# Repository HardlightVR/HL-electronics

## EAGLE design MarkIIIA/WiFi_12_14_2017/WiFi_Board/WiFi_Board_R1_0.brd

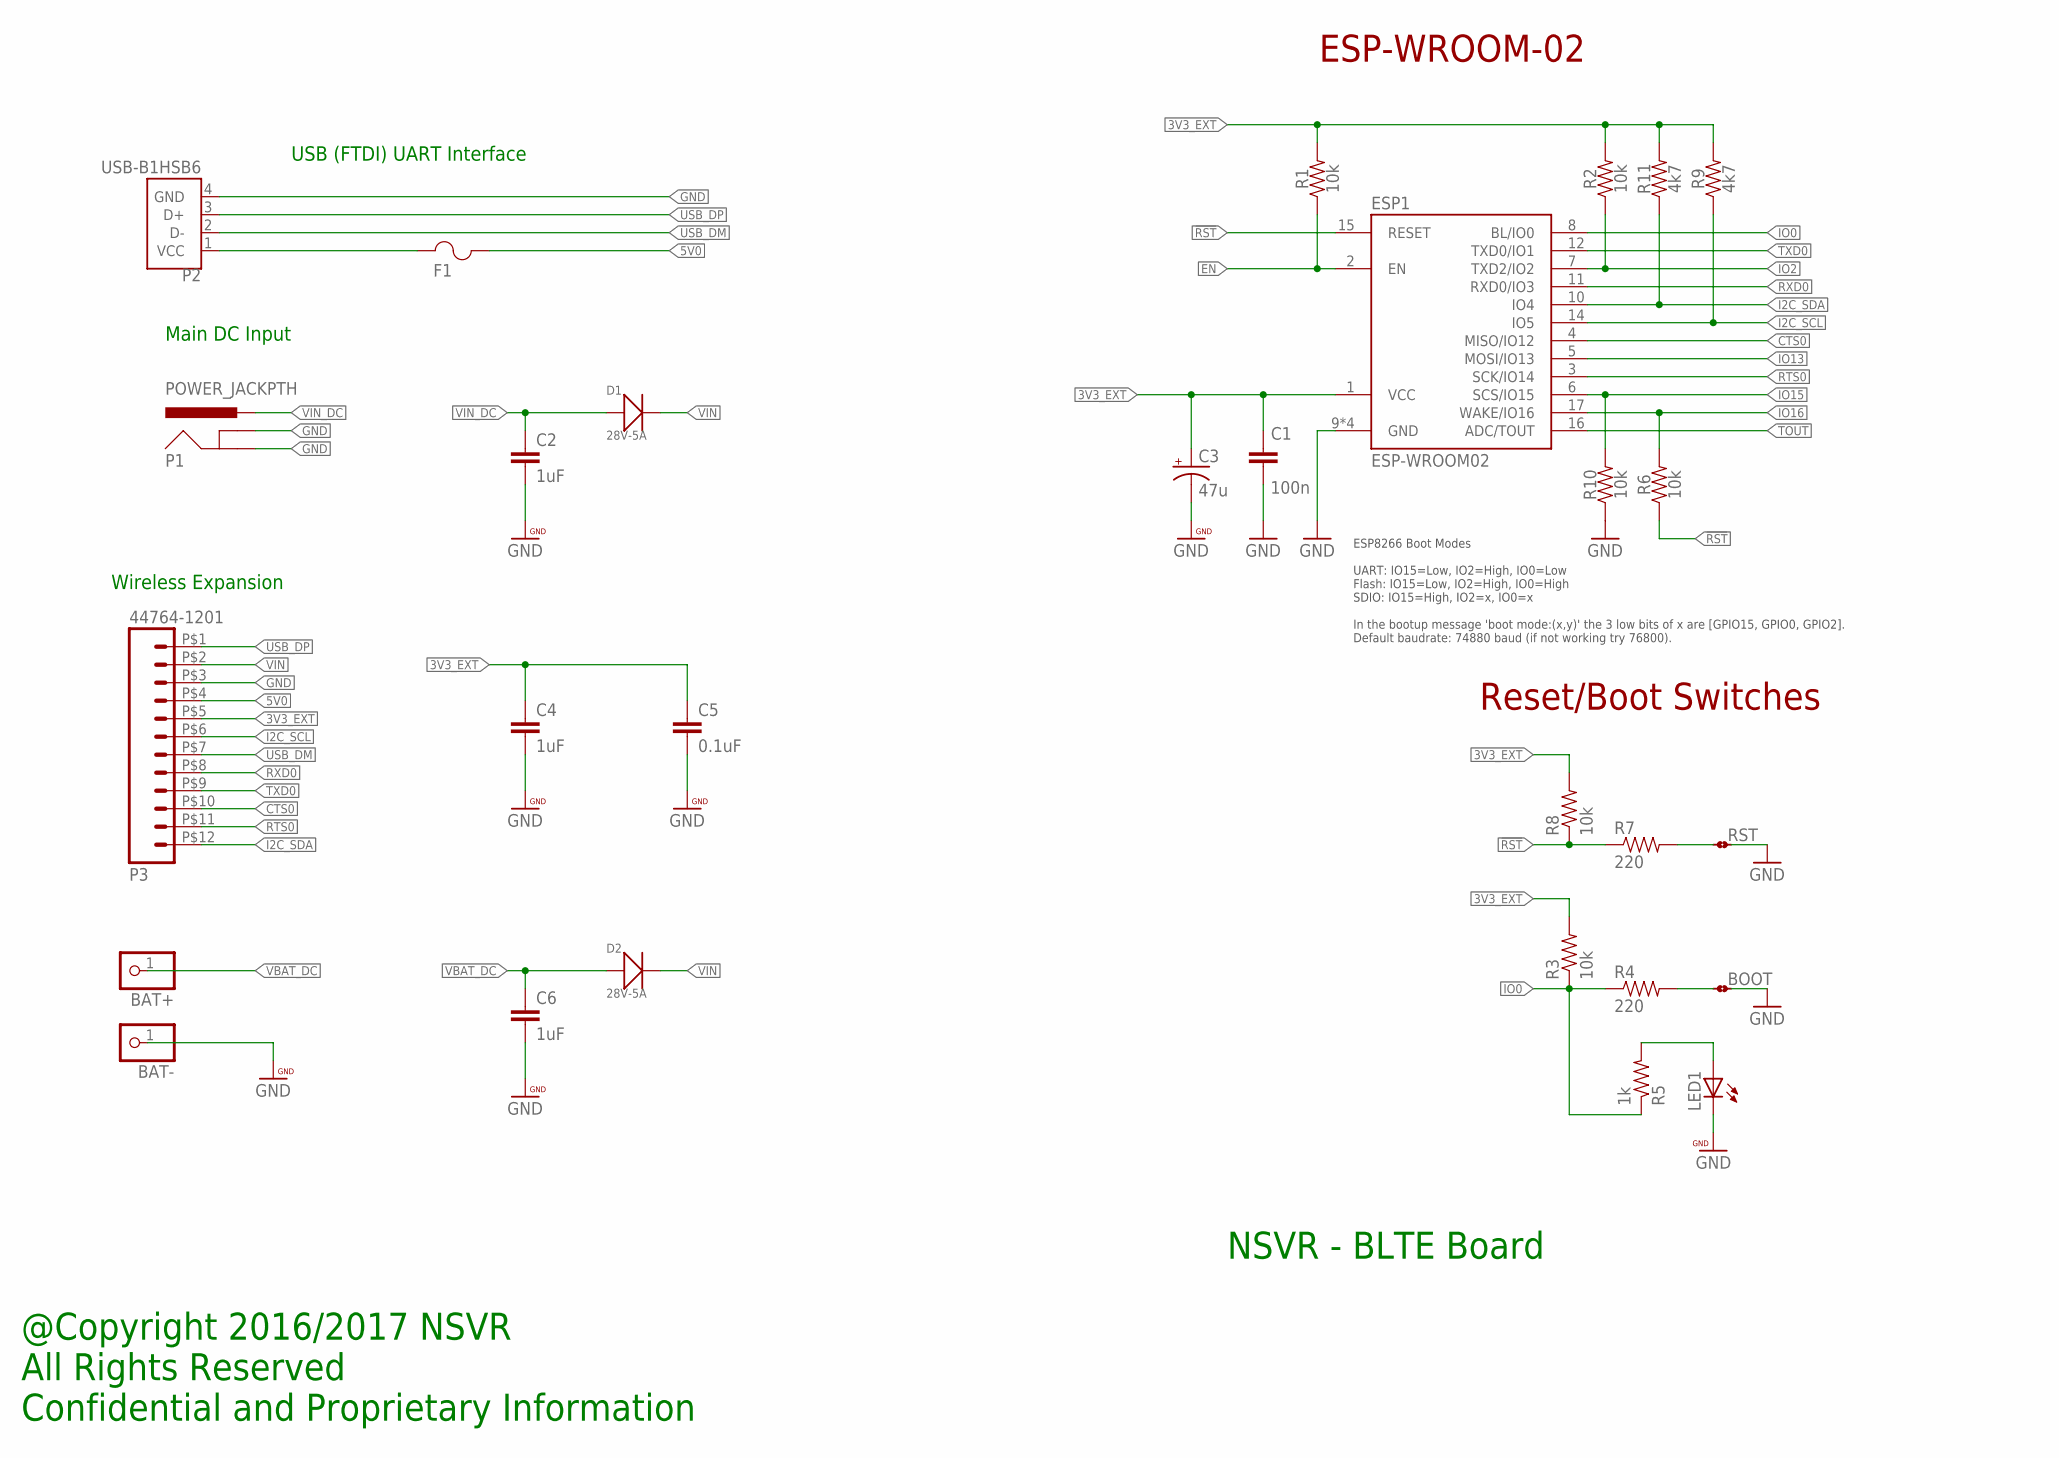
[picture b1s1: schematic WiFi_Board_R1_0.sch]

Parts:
BAT+: WPAD-1-PTH; WPAD-1-PTH-2.54
BAT-: WPAD-1-PTH; WPAD-1-PTH-2.54
BOOT: JMP-2-NO-PTH; JMP-2-NO-PTH-2.54
C1: 100n; 0402-CAP
C2, C4, C6: 1uF; 0402-CAP
C3: 47u; PANASONIC_D
C5: 0.1uF; 0402-CAP
D1, D2: 28V-5A; DO-214AA
ESP1: ESP-WROOM02
F1: 1206L050YR; 1206LSERIES
LED1: LEDCHIP-LED0603; CHIP-LED0603
P1: POWER_JACKPTH; POWER_JACK_PTH
P2: USB-B1HSB6; OST_USB-B1HSB6
P3: 44764-1201
R1, R2, R3, R6, R8, R10: 10k; EIA-0402
R4, R7: 220; EIA-0402
R5: 1k; EIA-0402
R9, R11: 4k7; EIA-0402
RST: JMP-2-NO-PTH; JMP-2-NO-PTH-2.54

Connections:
3V3_EXT: C1.2, C3.+, C4.1, C5.1, ESP1.1 (VCC), P3.P$5 (5), R1.2, R2.2, R3.2, R8.2, R9.2, R11.2
5V0: F1.2, P3.P$4 (4)
!RST: ESP1.15 (RESET), R6.1, R7.1, R8.1
CTS0: ESP1.4 (MISO/IO12), P3.P$10 (10)
EN: ESP1.2 (EN), R1.1
GND: BAT-.1, BOOT.2, C1.1, C2.2, C3.-, C4.2, C5.2, C6.2, ESP1.9 (GND), ESP1.13 (GND), ESP1.18 (GND), ESP1.TP (GND), LED1.C, P1.GND, P1.GNDBREAK, P2.4 (GND), P3.P$3 (3), R10.1, RST.2
I2C_SCL: ESP1.14 (IO5), P3.P$6 (6), R9.1
I2C_SDA: ESP1.10 (IO4), P3.P$12 (12), R11.1
IO0: ESP1.8 (BL/IO0), R3.1, R4.1, R5.1
IO2: ESP1.7 (TXD2/IO2), R2.1
IO13: ESP1.5 (MOSI/IO13)
IO15: ESP1.6 (SCS/IO15), R10.2
IO16: ESP1.17 (WAKE/IO16), R6.2
LED1: LED1.A, R5.2
unnamed: R7.2, RST.1
unnamed: BOOT.1, R4.2
RTS0: ESP1.3 (SCK/IO14), P3.P$11 (11)
RXD0: ESP1.11 (RXD0/IO3), P3.P$8 (8)
TOUT: ESP1.16 (ADC/TOUT)
TXD0: ESP1.12 (TXD0/IO1), P3.P$9 (9)
USB_DM: P2.2 (D-), P3.P$7 (7)
USB_DP: P2.3 (D+), P3.P$1 (1)
VBAT_DC: BAT+.1, C6.1, D2.+
VBUS_IN: F1.1, P2.1 (VCC)
VIN: D1.-, D2.-, P3.P$2 (2)
VIN_DC: C2.1, D1.+, P1.PWR

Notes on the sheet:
Wireless Expansion
Main DC Input
USB (FTDI) UART Interface
@Copyright 2016/2017 NSVR All Rights Reserved Confidential and Proprietary Information
NSVR - BLTE Board
ESP-WROOM-02
ESP8266 Boot Modes UART: IO15=Low, IO2=High, IO0=Low Flash: IO15=Low, IO2=High, IO0=High SDIO: IO15=High, IO2=x, IO0=x In the bootup message 'boot mode:(x,y)' the 3 low bits of x are [GPIO15, GPIO0, GPIO2]. Default baudrate: 74880 baud (if not working try 76800).
Reset/Boot Switches

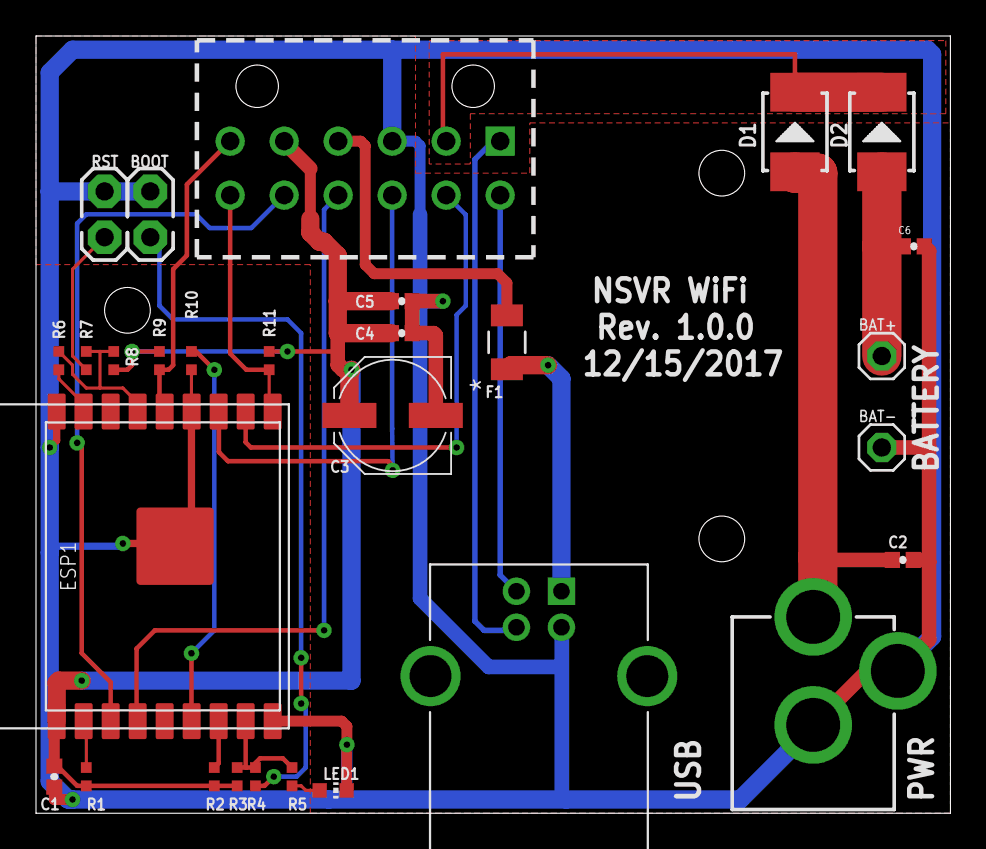
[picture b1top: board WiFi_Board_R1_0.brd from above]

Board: 2 copper layers, 50.8 x 43.2 mm, 29 parts (0 on the bottom side), 24 nets.

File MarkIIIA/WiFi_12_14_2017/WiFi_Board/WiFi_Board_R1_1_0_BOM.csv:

"Qty";"Value";"Device";"Package";"Parts";"Description";"";
"2";"";"JMP-2-NO-PTH";"JMP-2-NO-PTH-2.54";"BOOT, RST";"Two Terminal Jumper - Normally Open";"";
"1";"";"LEDCHIP-LED0603";"CHIP-LED0603";"LED1";"LED";"";
"2";"";"Tamiya Battery Cable";"Tamiya Battery Cable";"BAT+, BAT-";"Wire Pad - Single";"";
"1";"0.1uF";"CAP0402-CAP";"0402-CAP";"C5";"Capacitor";"";
"1";"100n";"CAP0402-CAP";"0402-CAP";"C1";"Capacitor";"";
"6";"10k";"RESISTOR0402-TYP";"EIA-0402";"R1, R2, R3, R6, R8, R10";"Resistor";"";
"1";"1206L050YR";"1206L050YR";"1206LSERIES";"F1";"6V/500mA PPTC";"";
"1";"1k";"RESISTOR0402-TYP";"EIA-0402";"R5";"Resistor";"";
"3";"1uF";"CAP0402-CAP";"0402-CAP";"C2, C4, C6";"Capacitor";"";
"2";"220";"RESISTOR0402-TYP";"EIA-0402";"R4, R7";"Resistor";"";
"2";"28V-5A";"SMD-DIODE-SCHOTTKY-28V-5A(DO-214AA)";"DO-214AA";"D1, D2";"304020021";"";
"1";"44764-1201";"44764-1201";"44764-1201";"P3";"";"";
"1";"47u";"CAP_POLD";"PANASONIC_D";"C3";"Capacitor Polarized";"";
"2";"4k7";"RESISTOR0402-TYP";"EIA-0402";"R9, R11";"Resistor";"";
"1";"ESP-WROOM02";"ESP-WROOM02";"ESP-WROOM02";"ESP1";"Espressif ESP-WROOM-02  and AI-Thinker ESP-12 ESP8266 WiFi/WLAN Module";"";
"1";"POWER_JACKPTH";"POWER_JACKPTH";"POWER_JACK_PTH";"P1";"Power Jack";"";
"1";"USB-B1HSB6";"USB-B1HSB6";"OST_USB-B1HSB6";"P2";"Conn Usb Type b r/a Black";"";

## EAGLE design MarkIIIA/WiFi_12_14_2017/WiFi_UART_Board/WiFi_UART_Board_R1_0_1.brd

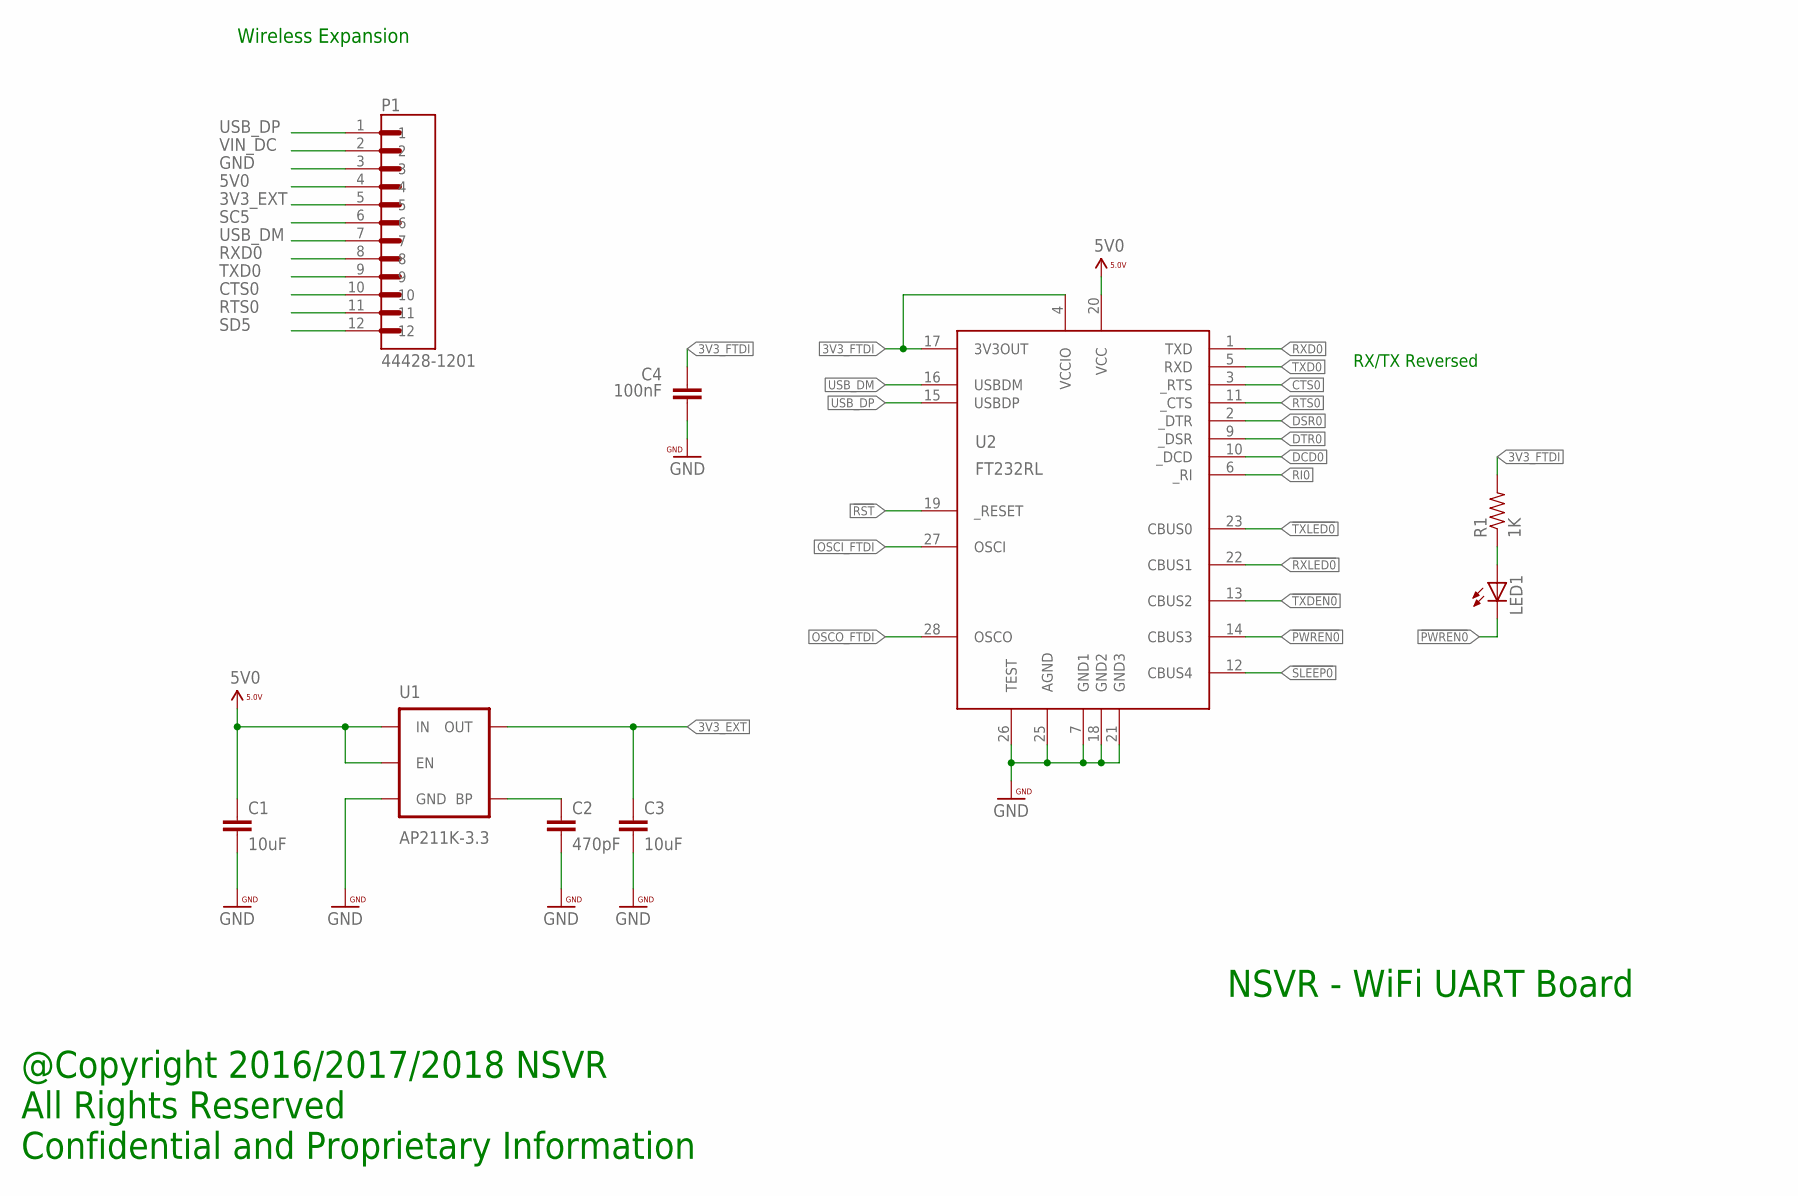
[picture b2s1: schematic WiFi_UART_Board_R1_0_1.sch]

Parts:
C1, C3: 10uF; 0603-CAP
C2: 470pF; 0402-CAP
C4: 100nF; 0402-CAP
LED1: LEDCHIP-LED0603; CHIP-LED0603
P1: 44428-1201; MOLEX_44428-1201
R1: 1K; EIA-0402
U1: AP211K-3.3; SOT23-5
U2: FT232RL; SSOP28DB

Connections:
3V3_EXT: C3.1, P1.5, U1.5 (OUT)
3V3_FTDI: C4.1, R1.2, U2.4 (VCCIO), U2.17 (3V3OUT)
5V0: C1.1, P1.4, U1.1 (IN), U1.3 (EN), U2.20 (VCC)
!PWREN0: LED1.C, U2.14 (CBUS3)
!RST: U2.19 (_RESET)
!RXLED0: U2.22 (CBUS1)
!SLEEP0: U2.12 (CBUS4)
!TXDEN0: U2.13 (CBUS2)
!TXLED0: U2.23 (CBUS0)
CTS0: P1.10, U2.3 (_RTS)
DCD0: U2.10 (_DCD)
DSR0: U2.2 (_DTR)
DTR0: U2.9 (_DSR)
GND: C1.2, C2.2, C3.2, C4.2, P1.3, U1.2 (GND), U2.7 (GND1), U2.18 (GND2), U2.21 (GND3), U2.25 (AGND), U2.26 (TEST)
unnamed: LED1.A, R1.1
unnamed: C2.1, U1.4 (BP)
OSCI_FTDI: U2.27 (OSCI)
OSCO_FTDI: U2.28 (OSCO)
RI0: U2.6 (_RI)
RTS0: P1.11, U2.11 (_CTS)
RXD0: P1.8, U2.1 (TXD)
SC5: P1.6
SD5: P1.12
TXD0: P1.9, U2.5 (RXD)
USB_DM: P1.7, U2.16 (USBDM)
USB_DP: P1.1, U2.15 (USBDP)
VIN_DC: P1.2

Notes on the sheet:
@Copyright 2016/2017/2018 NSVR All Rights Reserved Confidential and Proprietary Information
NSVR - WiFi UART Board
Wireless Expansion
RX/TX Reversed

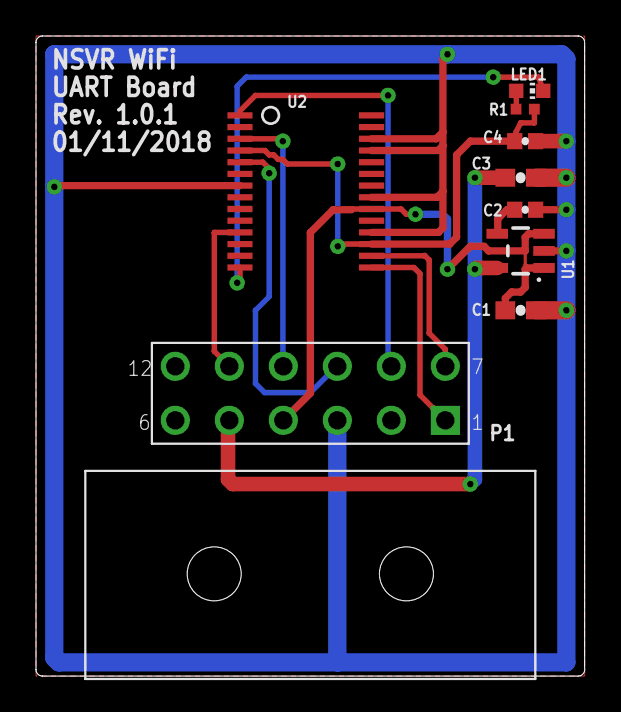
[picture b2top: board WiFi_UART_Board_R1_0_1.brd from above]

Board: 2 copper layers, 30.5 x 35.6 mm, 9 parts (0 on the bottom side), 13 nets.

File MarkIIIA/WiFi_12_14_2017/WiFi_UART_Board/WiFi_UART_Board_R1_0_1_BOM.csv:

"Qty";"Value";"Device";"Package";"Parts";"Description";"";
"1";"";"LEDCHIP-LED0603";"CHIP-LED0603";"LED1";"LED";"";
"1";"100nF";"CAP0402-CAP";"0402-CAP";"C4";"Capacitor";"";
"2";"10uF";"CAP0603-CAP";"0603-CAP";"C1, C3";"Capacitor";"";
"1";"1K";"RESISTOR0402-TYP";"EIA-0402";"R1";"Resistor";"";
"1";"3.3V/600mA";"AP2112K-3.3TRG1";"SOT23-5";"U1";"AP2112K-3";"";
"1";"44428-1201";"44428-1201";"MOLEX_44428-1201";"P1";"Conn Wire to Board HDR 12 POS 3mm Solder RA Thru-Hole Micro-Fit 3.0 BMI? Tray";"";
"1";"470pF";"CAP0402-CAP";"0402-CAP";"C2";"Capacitor";"";
"1";"FT232RL";"FT232RL";"SSOP28DB";"U2";"USB UART";"";

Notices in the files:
parts and their libraries:
SparkFun-Connectors: Licensing: Creative Commons ShareAlike 4.0 International - https://creativecommons.org/licenses/by-sa/4.0
PatternAgents-ProtoPads: License : http://creativecommons.org/licenses/by-sa/4.0
(Creative Commons 4.0)
COPYRIGHT: Copyright C 2015 Accelerated Designs. All rights reserved
